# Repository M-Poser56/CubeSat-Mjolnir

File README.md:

# CubeSat-Mjolnir
Repository for the Mjolnir CubeSat personal project, tracking all code and design material.

The Mjolnir CubeSat is a 10cm by 10cm by 10cm (1U) microsatellite complete with an onboard flight computer, sensor telemetry, radio module, a camera module, custom onboard BMS, onboard attitude control via reaction wheels and custom motor control PCB.

There is also a fully custom groundstation consisting of a python backend and JS frontend, meant to interface with an Arduino Uno running a script to interface with a matching LoRa radio module to the CubeSat.

Had a blast making this, design doc covers everything and is worth a read!

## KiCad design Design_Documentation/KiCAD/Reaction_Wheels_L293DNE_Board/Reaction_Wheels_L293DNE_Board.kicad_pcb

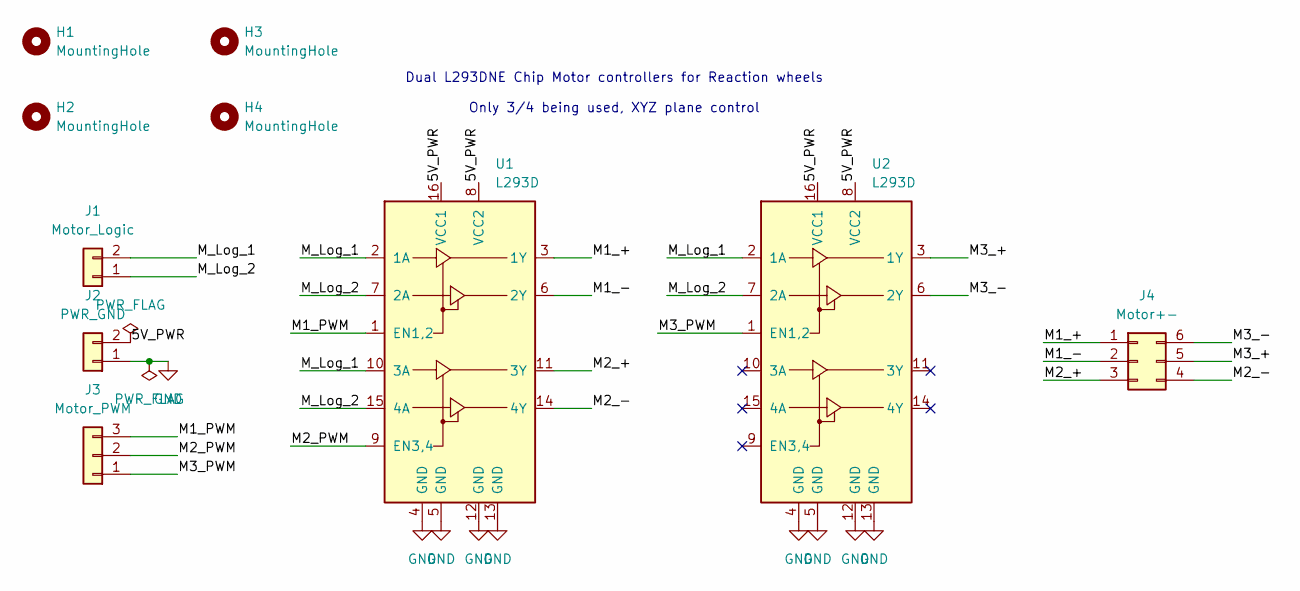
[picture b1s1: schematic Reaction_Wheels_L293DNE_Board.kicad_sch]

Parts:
H1, H2, H3, H4: MountingHole; MountingHole_3.2mm_M3
J1: Motor_Logic; PinHeader_1x02_P2.54mm_Vertical
J2: PWR_GND; PinHeader_1x02_P2.54mm_Vertical
J3: Motor_PWM; PinHeader_1x03_P2.54mm_Vertical
J4: Motor+-; PinHeader_2x03_P2.54mm_Vertical
U1, U2: L293D; DIP-16_W7.62mm

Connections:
/5V_PWR: J2.2, U1.8 (VCC2), U1.16 (VCC1), U2.8 (VCC2), U2.16 (VCC1)
/M1_+: J4.1, U1.3 (1Y)
/M1_-: J4.2, U1.6 (2Y)
/M1_PWM: J3.3, U1.1 (EN1,2)
/M2_+: J4.3, U1.11 (3Y)
/M2_-: J4.4, U1.14 (4Y)
/M2_PWM: J3.2, U1.9 (EN3,4)
/M3_+: J4.5, U2.3 (1Y)
/M3_-: J4.6, U2.6 (2Y)
/M3_PWM: J3.1, U2.1 (EN1,2)
/M_Log_1: J1.2, U1.2 (1A), U1.10 (3A), U2.2 (1A)
/M_Log_2: J1.1, U1.7 (2A), U1.15 (4A), U2.7 (2A)
GND: J2.1, U1.4 (GND), U1.5 (GND), U1.12 (GND), U1.13 (GND), U2.4 (GND), U2.5 (GND), U2.12 (GND), U2.13 (GND)

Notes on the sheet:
Dual L293DNE Chip Motor controllers for Reaction wheels Only 3/4 being used, XYZ plane control

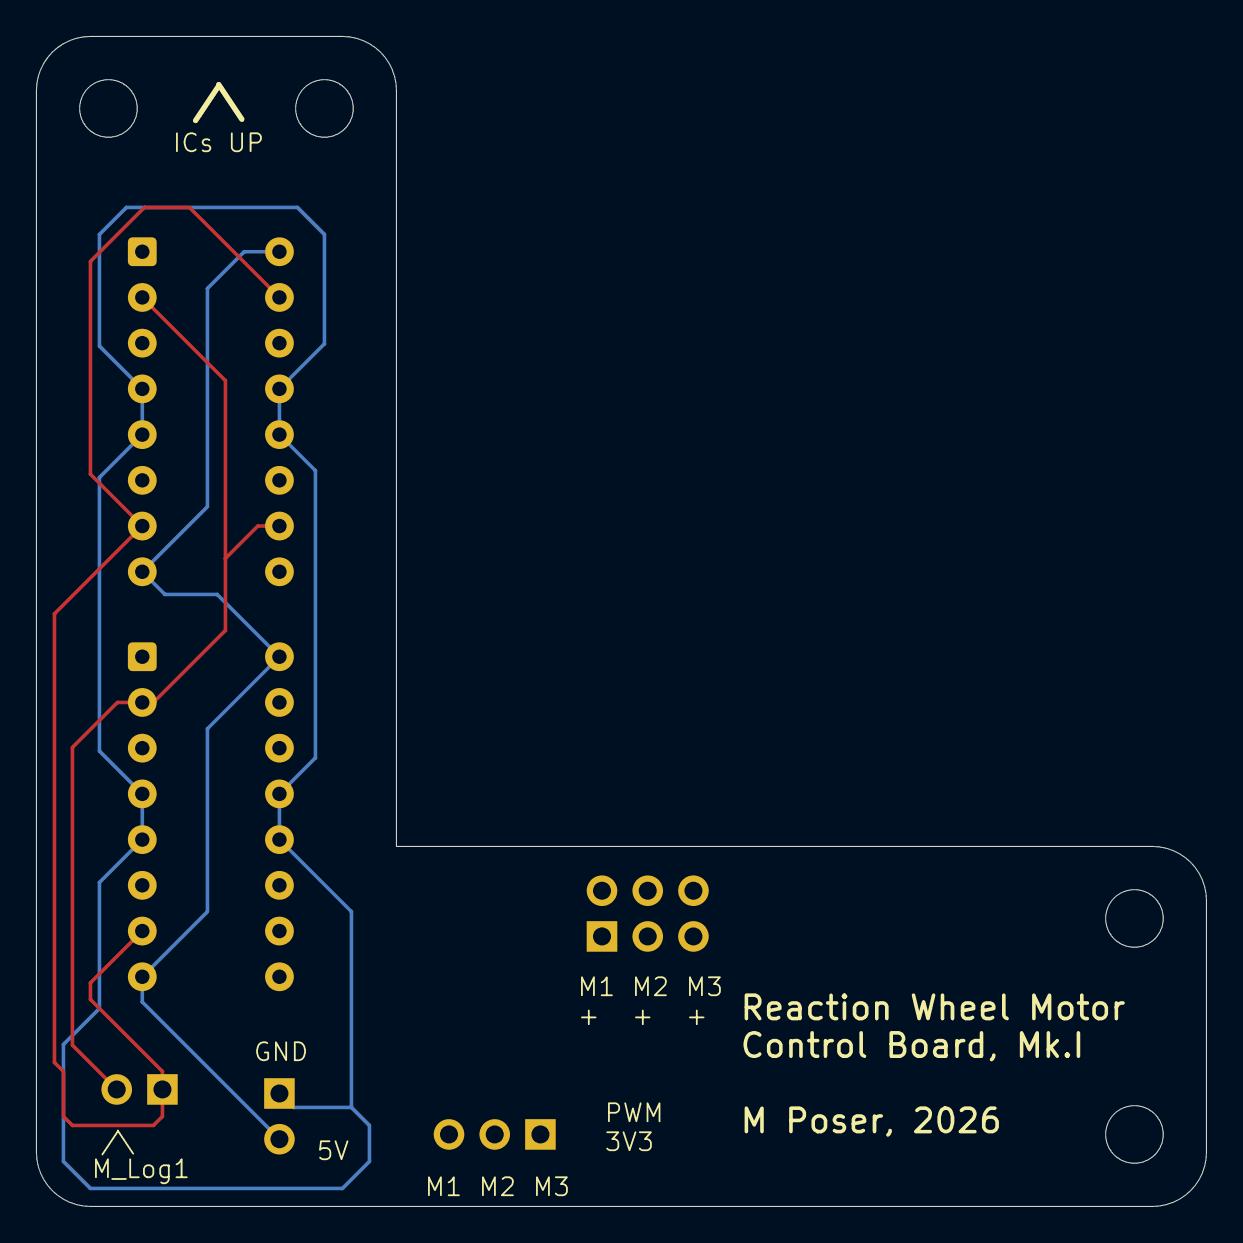
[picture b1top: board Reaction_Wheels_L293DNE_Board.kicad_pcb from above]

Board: 4 copper layers, 65.0 x 65.0 mm, 10 parts (0 on the bottom side), 13 nets.

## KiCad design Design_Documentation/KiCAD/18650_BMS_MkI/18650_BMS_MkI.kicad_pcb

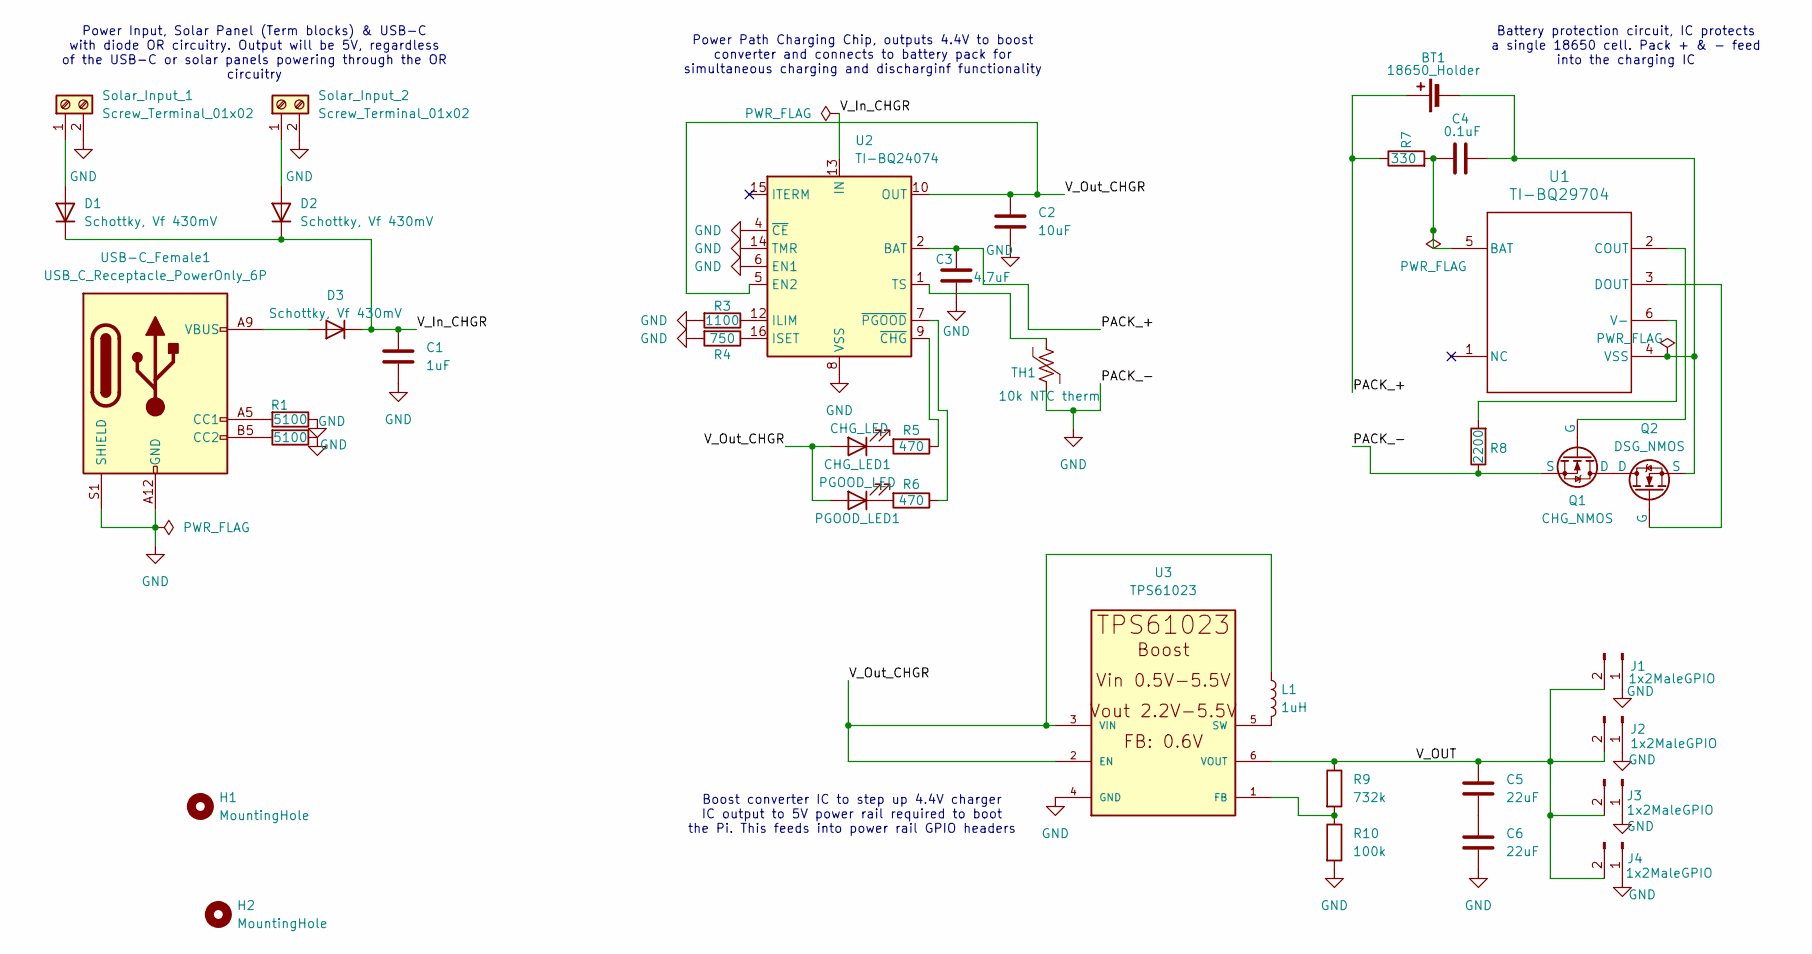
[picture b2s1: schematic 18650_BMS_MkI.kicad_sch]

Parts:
BT1: 18650_Holder; BatteryHolder_Keystone_1042_1x18650
C1: 1uF; C_0603_1608Metric
C2: 10uF; C_0603_1608Metric
C3: 4.7uF; C_0603_1608Metric
C4: 0.1uF; C_0603_1608Metric
C5, C6: 22uF; C_1206_3216Metric
CHG_LED1: CHG_LED; LED_1206_3216Metric
D1, D2, D3: Schottky, Vf 430mV; D_SMB
H1, H2: MountingHole; MountingHole_3.2mm_M3
J1, J2, J3, J4: 1x2MaleGPIO; PinHeader_1x02_P2.54mm_Vertical
L1: 1uH; L_1210_3225Metric
PGOOD_LED1: PGOOD_LED; LED_1206_3216Metric
Q1: CHG_NMOS; SOT-23-3
Q2: DSG_NMOS; SOT-23-3
R1, R2: 5100; R_0603_1608Metric
R3: 1100; R_0603_1608Metric
R4: 750; R_0603_1608Metric
R5, R6: 470; R_0603_1608Metric
R7: 330; R_0603_1608Metric
R8: 2200; R_0603_1608Metric
R9: 732k; R_0603_1608Metric
R10: 100k; R_0603_1608Metric
Solar_Input_1, Solar_Input_2: Screw_Terminal_01x02; TerminalBlock_Phoenix_PT-1,5-2-5.0-H_1x02_P5.00mm_Horizontal
TH1: 10k NTC therm; R_0603_1608Metric
U1: TI-BQ29704; DSE0006A
U2: TI-BQ24074; VQFN-16-1EP_3x3mm_P0.5mm_EP1.6x1.6mm_ThermalVias
U3: TPS61023; SOT-563; DigiKey_Part_Number 296-TPS61023DRLRCT-ND
USB-C_Female1: USB_C_Receptacle_PowerOnly_6P; USB_C_Receptacle_GCT_USB4125-xx-x_6P_TopMnt_Horizontal

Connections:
/PACK_+: BT1.1 (+), C3.1, R7.1, U2.2 (BAT), U2.3 (BAT)
/V_In_CHGR: C1.1, D1.1 (K), D2.1 (K), D3.1 (K), U2.13 (IN)
/V_OUT: C5.1, J1.2, J2.2, J3.2, J4.2, R9.1, U3.6 (VOUT)
/V_Out_CHGR: C2.1, CHG_LED1.2 (A), L1.1, PGOOD_LED1.2 (A), U2.5 (EN2), U2.10 (OUT), U2.11 (OUT), U3.2 (EN), U3.3 (VIN)
GND: C1.2, C2.2, C3.2, C6.2, J1.1, J2.1, J3.1, J4.1, Q1.3 (S), R1.1, R2.1, R3.2, R4.2, R8.1, R10.2, Solar_Input_1.2, Solar_Input_2.2, TH1.2, U2.4 (~CE), U2.6 (EN1), U2.8 (VSS), U2.14 (TMR), U2.17 (VSS), U3.4 (GND), USB-C_Female1.A12 (GND), USB-C_Female1.B12 (GND), USB-C_Female1.S1 (SHIELD)
unnamed: BT1.2 (-), C4.1, Q2.3 (S), U1.4 (VSS)
unnamed: C5.2, C6.1
unnamed: CHG_LED1.1 (K), R5.2
unnamed: D1.2 (A), Solar_Input_1.1
unnamed: D2.2 (A), Solar_Input_2.1
unnamed: D3.2 (A), USB-C_Female1.A9 (VBUS), USB-C_Female1.B9 (VBUS)
unnamed: PGOOD_LED1.1 (K), R6.2
unnamed: Q1.1 (D), Q2.1 (D)
unnamed: Q1.2 (G), U1.2 (COUT)
unnamed: Q2.2 (G), U1.3 (DOUT)
unnamed: C4.2, R7.2, U1.5 (BAT)
unnamed: R8.2, U1.6 (V-)
unnamed: R3.1, U2.12 (ILIM)
unnamed: R4.1, U2.16 (ISET)
unnamed: TH1.1, U2.1 (TS)
unnamed: R5.1, U2.9 (~CHG)
unnamed: R6.1, U2.7 (~PGOOD)
unnamed: R9.2, R10.1, U3.1 (FB)
unnamed: L1.2, U3.5 (SW)
unnamed: R1.2, USB-C_Female1.A5 (CC1)
unnamed: R2.2, USB-C_Female1.B5 (CC2)

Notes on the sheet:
Battery protection circuit, IC protects a single 18650 cell. Pack + & - feed into the charging IC
Boost converter IC to step up 4.4V charger IC output to 5V power rail required to boot the Pi. This feeds into power rail GPIO headers
Power Path Charging Chip, outputs 4.4V to boost converter and connects to battery pack for simultaneous charging and discharginf functionality
Power Input, Solar Panel (Term blocks) & USB-C with diode OR circuitry. Output will be 5V, regardless of the USB-C or solar panels powering through the OR circuitry

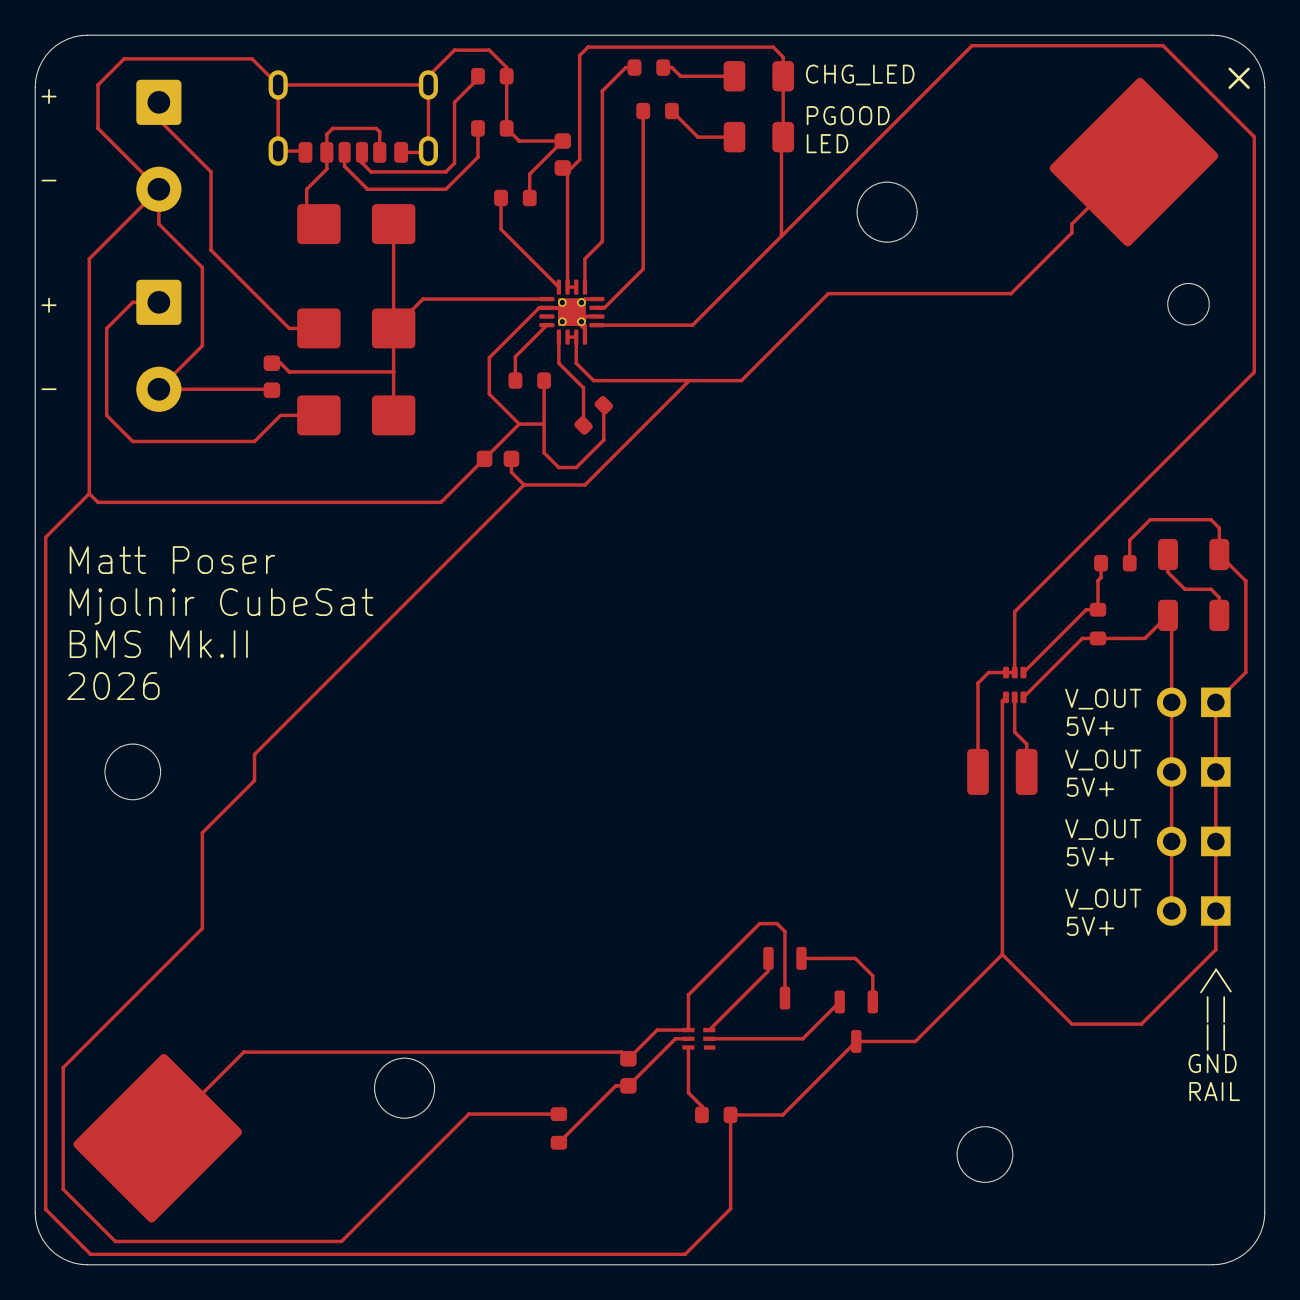
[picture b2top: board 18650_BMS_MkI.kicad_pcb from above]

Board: 2 copper layers, 70.7 x 70.7 mm, 38 parts (0 on the bottom side), 26 nets.

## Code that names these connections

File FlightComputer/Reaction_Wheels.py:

#downstream script for reaction wheels functionality

#this will follow the same (rough) architecture as the Mjolnir_Reboot.py and
#Star_tracker.py scripts, but will be a little bit more depth

#this script, will take in command information, and after some initialization of
#GPIO output & PWM pins, update the state of the onboard reaction wheel controls
#the flow of the script will recieve messages in the same way as the other two,
#but will update GPIO settings instead of running a subprocess command function

import queue
import paho.mqtt.client as mqtt
import RPi.GPIO as GPIO
import re

reactionwheels_queue = queue.Queue() #initialize script local queue to store upstream command messages


#mqtt functions (for reboot script)
def on_connect(client, userdata, flags, reason_code, properties):
    print(f"mqtt localhost connected with result code {reason_code}")
    client.subscribe("CMD/REACTIONWHEELS") #upstream being published to by LoRA_ULDL in the CommandHandler() function

def on_message(client, userdata, msg):
    reactionwheels_queue.put(msg.payload.decode()) #adds command string to queue, FIFO

ReactionWheels_client = mqtt.Client(mqtt.CallbackAPIVersion.VERSION2)
ReactionWheels_client.on_connect = on_connect
ReactionWheels_client.on_message = on_message
ReactionWheels_client.connect("localhost", 1883)
ReactionWheels_client.loop_start()

#GPIO initialization
motor_logic_switch = [GPIO.LOW,GPIO.LOW] #digital directionality pins, 1/0 and 0/1 for CW/CCW. These are pins 16, 18 in order
motor_logic_pins = [16, 18]
M1_pwm_pin = 29 #all physical board pins
M2_pwm_pin = 31
M3_pwm_pin = 37
pwm_Hz = 490 #matches arduino Uno test frequency
GPIO.setmode(GPIO.BOARD)
GPIO.setwarnings(False)

#motor logic setup
GPIO.setup(motor_logic_pins[0], GPIO.OUT, initial=GPIO.LOW)
GPIO.setup(motor_logic_pins[1], GPIO.OUT, initial=GPIO.LOW)
#motor pwm setup, start all at 0% pwm
GPIO.setup(M1_pwm_pin, GPIO.OUT)
GPIO.setup(M2_pwm_pin, GPIO.OUT)
GPIO.setup(M3_pwm_pin, GPIO.OUT)
M1_pwm = GPIO.PWM(M1_pwm_pin, pwm_Hz)
M2_pwm = GPIO.PWM(M2_pwm_pin, pwm_Hz)
M3_pwm = GPIO.PWM(M3_pwm_pin, pwm_Hz)
M1_pwm.start(0)
M2_pwm.start(0)
M3_pwm.start(0)
#initialize p1, p2, p3 values ahead of time for thoroughness (also for first command)
p1 = 0
p2 = 0
p3 = 0



try:
    while True:
        recieved_command = reactionwheels_queue.get()

        #first step is to parse the string, to determine both the direction of the wheels
        #and the values of each PWM to update string is of the below form:
        #"CMD:REACTIONWHEELS{INT,INT,INT}" where any of the ints can be signed either way
        match = re.fullmatch(r"CMD:REACTIONWHEELS\{(-?\d+),(-?\d+),(-?\d+)\}", recieved_command)
        if match:
            p1, p2, p3 = (int(g) for g in match.groups()) #pulls the ints out of the string, as ints

        #2 - determine if first int is negative (and change logic accordingly)
        if p1 < 0:
            motor_logic_switch = [GPIO.LOW, GPIO.HIGH]
        else:
            motor_logic_switch = [GPIO.HIGH, GPIO.LOW]
        #set logic/direction states
        GPIO.output(motor_logic_pins[0], motor_logic_switch[0])
        GPIO.output(motor_logic_pins[1], motor_logic_switch[1])

        #3 - update PWM values for each individual object, based on p1/p2/p3
        #safety check, if inputted pwm% (pn variable) is over 100, set to 0
        if abs(p1) > 100:
            p1 = 0
        if abs(p2) > 100:
            p2 = 0
        if abs(p3) > 100:
            p3 = 0
        #set pwm values
        M1_pwm.ChangeDutyCycle(abs(p1))
        M2_pwm.ChangeDutyCycle(abs(p2))
        M3_pwm.ChangeDutyCycle(abs(p3))
        

finally:
        print("Reaction Wheel motor control Script Deactivated")
        ReactionWheels_client.loop_stop()
        ReactionWheels_client.disconnect()
        M1_pwm.stop()
        M2_pwm.stop()
        M3_pwm.stop()
        GPIO.cleanup()
